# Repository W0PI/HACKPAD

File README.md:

# HACKPAD
a little macro pad with 5 key switches 1 rotary encoder and a oled screen run but the rp2040 xiao

just front stuff

just back stuff

front pcb componants

back pcb componants

front pcb

back pcb

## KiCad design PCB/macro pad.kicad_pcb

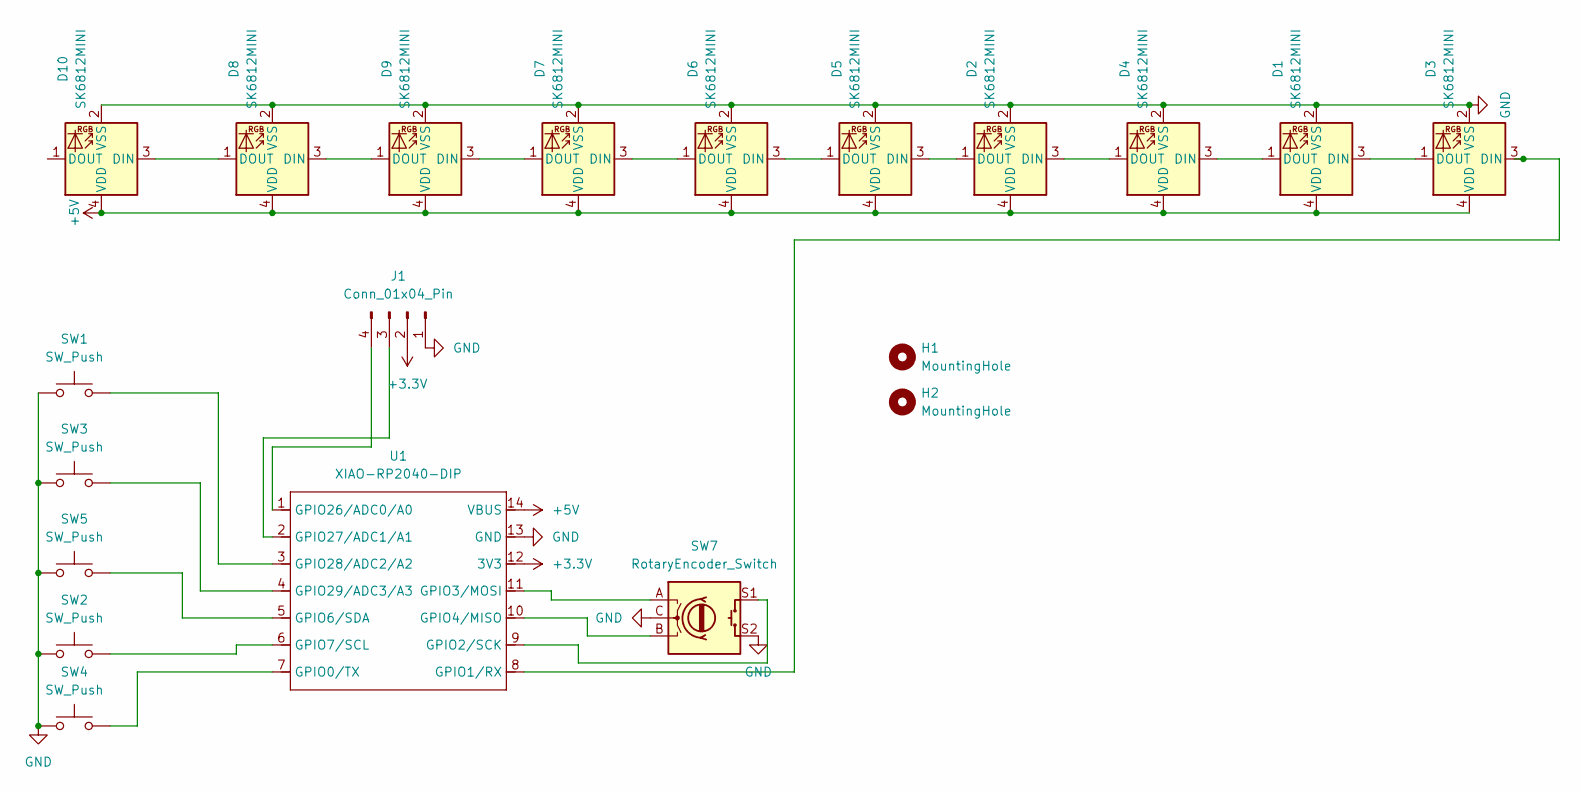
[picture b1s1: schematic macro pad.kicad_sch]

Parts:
D1, D2, D3, D4, D5, D6, D7, D8, D9, D10: SK6812MINI; LED_SK6812MINI_PLCC4_3.5x3.5mm_P1.75mm
H1, H2: MountingHole; MountingHole_3.2mm_M3
J1: Conn_01x04_Pin; SSD1306-0.91-OLED-4pin-128x32
SW1, SW2, SW3, SW4, SW5: SW_Push; SW_Cherry_MX_1.00u_PCB
SW7: RotaryEncoder_Switch; RotaryEncoder_Alps_EC11E-Switch_Vertical_H20mm
U1: XIAO-RP2040-DIP

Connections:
+3.3V: J1.2, U1.12 (3V3)
+5V: D1.4 (VDD), D2.4 (VDD), D3.4 (VDD), D4.4 (VDD), D5.4 (VDD), D6.4 (VDD), D7.4 (VDD), D8.4 (VDD), D9.4 (VDD), D10.4 (VDD), U1.14 (VBUS)
GND: D1.2 (VSS), D2.2 (VSS), D3.2 (VSS), D4.2 (VSS), D5.2 (VSS), D6.2 (VSS), D7.2 (VSS), D8.2 (VSS), D9.2 (VSS), D10.2 (VSS), J1.1, SW1.1, SW2.1, SW3.1, SW4.1, SW5.1, SW7.C, SW7.S2, U1.13 (GND)
unnamed: D1.3 (DIN), D3.1 (DOUT)
unnamed: D1.1 (DOUT), D4.3 (DIN)
unnamed: D2.3 (DIN), D4.1 (DOUT)
unnamed: D2.1 (DOUT), D5.3 (DIN)
unnamed: D3.3 (DIN), U1.8 (GPIO1/RX)
unnamed: D5.1 (DOUT), D6.3 (DIN)
unnamed: D6.1 (DOUT), D7.3 (DIN)
unnamed: D7.1 (DOUT), D9.3 (DIN)
unnamed: D8.3 (DIN), D9.1 (DOUT)
unnamed: D8.1 (DOUT), D10.3 (DIN)
unnamed: J1.3, U1.2 (GPIO27/ADC1/A1)
unnamed: J1.4, U1.1 (GPIO26/ADC0/A0)
unnamed: SW4.2, U1.7 (GPIO0/TX)
unnamed: SW7.S1, U1.9 (GPIO2/SCK)
unnamed: SW7.A, U1.11 (GPIO3/MOSI)
unnamed: SW7.B, U1.10 (GPIO4/MISO)
unnamed: SW5.2, U1.5 (GPIO6/SDA)
unnamed: SW2.2, U1.6 (GPIO7/SCL)
unnamed: SW1.2, U1.3 (GPIO28/ADC2/A2)
unnamed: SW3.2, U1.4 (GPIO29/ADC3/A3)

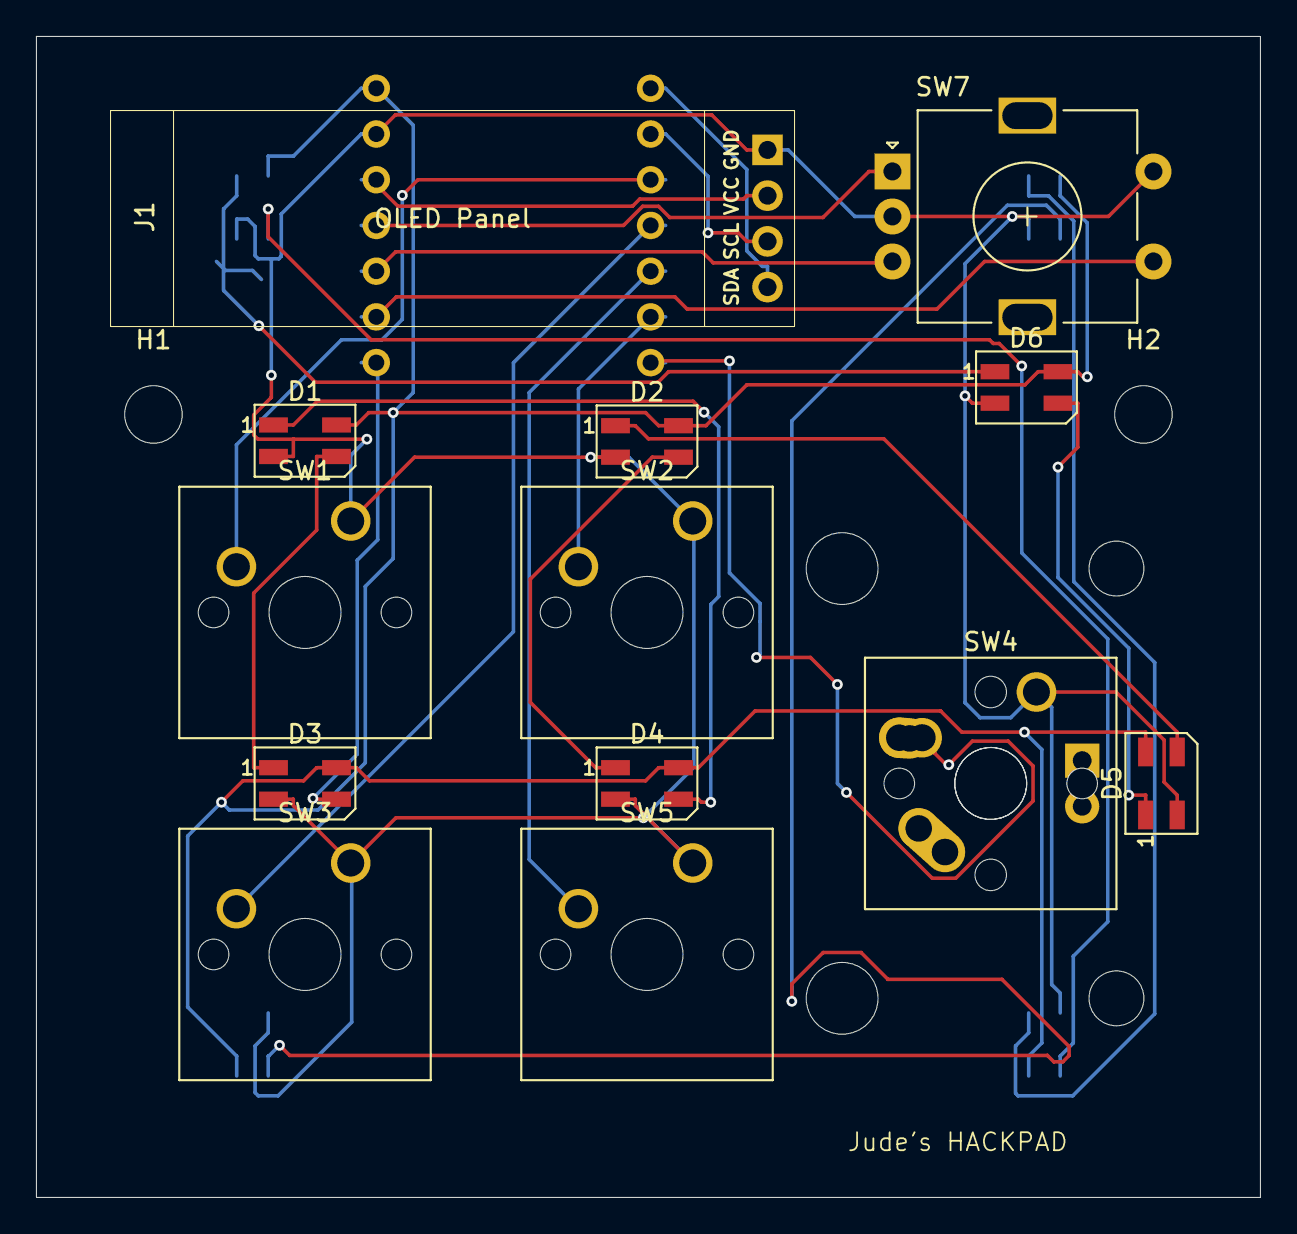
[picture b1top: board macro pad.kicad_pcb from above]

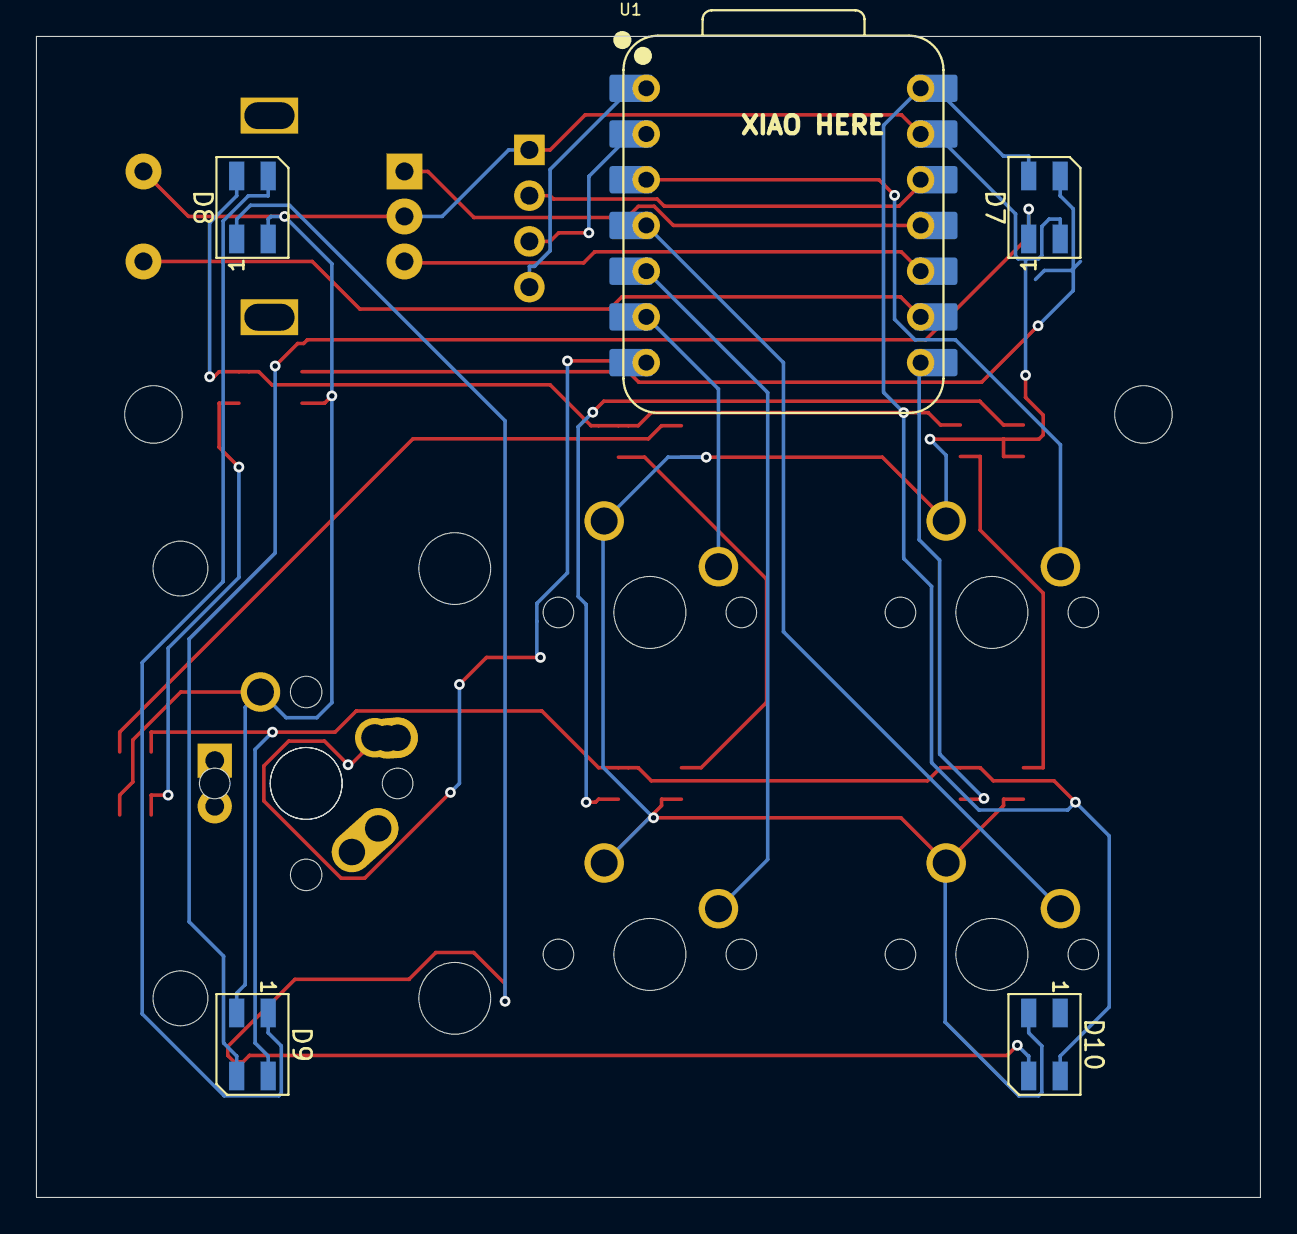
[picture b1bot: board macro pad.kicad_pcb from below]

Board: 2 copper layers, 68.0 x 64.5 mm, 20 parts (5 on the bottom side), 23 nets.

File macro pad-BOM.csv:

"Reference","Qty","Value","DNP","Exclude from BOM","Exclude from Board","Footprint","Datasheet"
"D1,D2,D3,D4,D5,D6,D7,D8,D9,D10","10","SK6812MINI","","","","LED_SMD:LED_SK6812MINI_PLCC4_3.5x3.5mm_P1.75mm","https://cdn-shop.adafruit.com/product-files/2686/SK6812MINI_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"
"H1,H2","2","MountingHole","","Excluded from BOM","","MountingHole:MountingHole_3.2mm_M3","~"
"J1","1","Conn_01x04_Pin","","","","SCREEN:SSD1306-0.91-OLED-4pin-128x32","~"
"SW1,SW2,SW3,SW4,SW5","5","SW_Push","","","","Button_Switch_Keyboard:SW_Cherry_MX_1.00u_PCB","~"
"SW7","1","RotaryEncoder_Switch","","","","Rotary_Encoder:RotaryEncoder_Alps_EC11E-Switch_Vertical_H20mm","~"
"U1","1","XIAO-RP2040-DIP","","","","OPL:XIAO-RP2040-DIP",""

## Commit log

2025-12-14 Add project files
2025-12-16 Create CAD
